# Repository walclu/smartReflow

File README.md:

# smartReflow
## Repository for STM32WB55 based reflow toaster oven controller

The smartReflowV2 is a STm32WB55 based toaster oven reflow controller for reflowing PCBs at home. 

## Features
- 2 SSR outputs
- 2 cooling fan outputs
- 2 MAX31855 temperature ADCs
- Buzzer
- Touch screen (Nextion 2.4" UART Display)
- Bluetooth low energy, onboard chip antenna with matching
- 2 virtual com ports 
- MATLAB data streaming
- EEPROM for storing custom profiles
- PLA drying mode

## Assembly
The PCB was made by JLCPCB and assembled by hand.

## Results
The oven follows the desired temperature profile with only 5% of total error (Reflow state is a little bit delayed at the end).

QFN28 soldering results with 138 C paste profile. No need of rework had to be done.

Finished oven

## ToDos
- Bluetooth works, but an interface (i.e. app) is needed
- Firmware is hard to read
- PCB outline is too small (Nextion Display does not fit nicely onto it)
- EEPROM usage not implemented
- PID autotune code

## License
MIT

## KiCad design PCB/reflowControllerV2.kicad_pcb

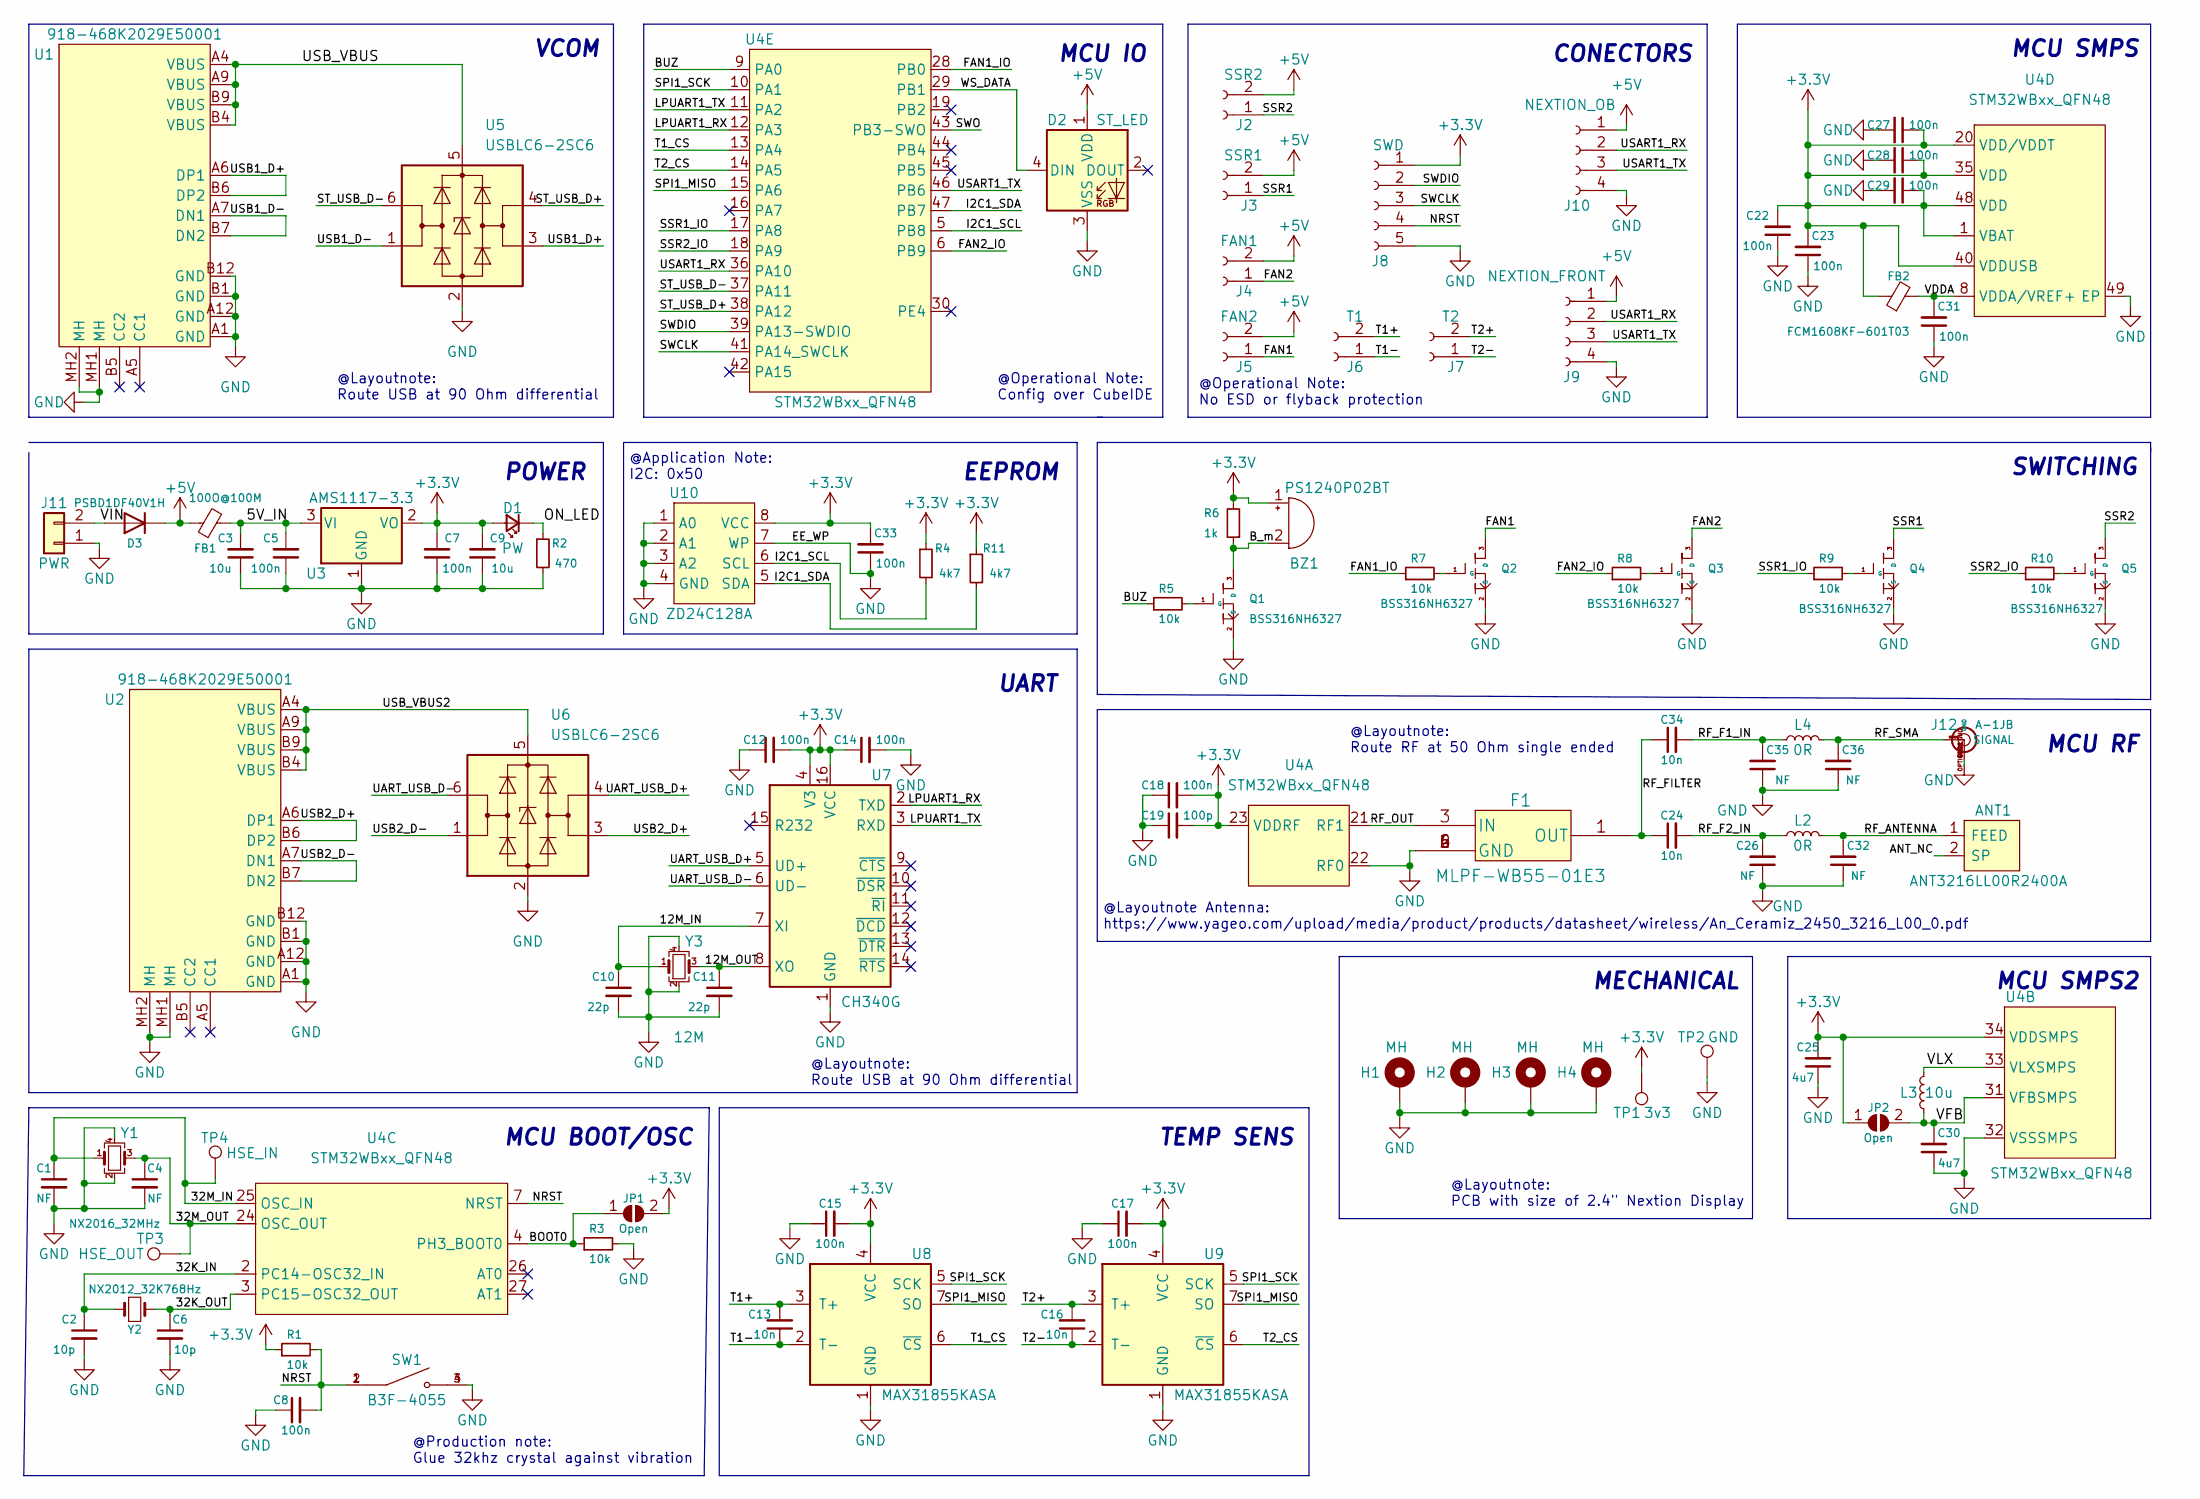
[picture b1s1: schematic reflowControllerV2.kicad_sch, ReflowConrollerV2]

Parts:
ANT1: ANT3216LL00R2400A; Mouser Part Number 603-ANT3216LL00R2400
BZ1: PS1240P02BT; Buzzer_TDK_PS1240P02BT_D12.2mm_H6.5mm
C1, C4, C26, C32, C35, C36: NF; C_0402_1005Metric
C2, C6: 10p; C_0402_1005Metric
C3, C9: 10u; C_0603_1608Metric
C5, C7, C8, C12, C14, C15, C17, C33: 100n; C_0603_1608Metric
C10, C11: 22p; C_0402_1005Metric
C13, C16: 10n; C_0805_2012Metric
C18, C22, C23, C27, C28, C29, C31: 100n; C_0402_1005Metric
C19: 100p; C_0402_1005Metric
C24, C34: 10n; C_0402_1005Metric
C25, C30: 4u7; C_0402_1005Metric
D1: PW; LED_0603_1608Metric
D2: ST_LED; LED_WS2812B_PLCC4_5.0x5.0mm_P3.2mm
D3: PSBD1DF40V1H; D_SOD-123F
F1: MLPF-WB55-01E3
FB1: 100O@100M; L_0603_1608Metric
FB2: FCM1608KF-601T03; L_0603_1608Metric
H1, H2, H3, H4: MH; MountingHole_3.2mm_M3_Pad_Via
J2: SSR2; JST_254_2P_V
J3: SSR1; JST_254_2P_V
J4: FAN1; JST_254_2P_V
J5: FAN2; JST_254_2P_V
J6: T1; JST_254_2P_V
J7: T2; JST_254_2P_V
J8: SWD; JST_254_5P_V
J9: NEXTION_FRONT; JST_254_4P_V
J10: NEXTION_OB; JST_254_4P_H
J11: PWR; TerminalBlock_Phoenix_MKDS-1,5-2_1x02_P5.00mm_Horizontal
J12: A-1JB; AMPHENOL_A-1JB
JP1, JP2: Open; R_0603_1608Metric
L2, L4: 0R; L_0402_1005Metric
L3: 10u; L_0603_1608Metric
Q1, Q2, Q3, Q4, Q5: BSS316NH6327; SOT-23
R1, R5, R7, R8, R9, R10: 10k; R_0603_1608Metric
R2: 470; R_0603_1608Metric
R3: 10k; R_0402_1005Metric
R4, R11: 4k7; R_0603_1608Metric
R6: 1k; R_0603_1608Metric
SW1: B3F-4055; SW_B3F-4055; PARTREV A070-E1-08
TP1: 3v3; TestPoint_Pad_D2.0mm
TP2: GND; TestPoint_Pad_D2.0mm
TP3: HSE_OUT; TestPoint_Pad_D1.0mm
TP4: HSE_IN; TestPoint_Pad_D1.0mm
U1, U2: 918-468K2029E50001
U3: AMS1117-3.3; SOT-223-3_TabPin2
U4: STM32WBxx_QFN48; QFN50P700X700X60-49N
U5, U6: USBLC6-2SC6; SOT-23-6
U7: CH340G; SOIC-16_3.9x9.9mm_P1.27mm
U8, U9: MAX31855KASA; SOIC-8_3.9x4.9mm_P1.27mm
U10: ZD24C128A; SOP-8_3.9x4.9mm_P1.27mm
Y1: NX2016_32MHz; Crystal_SMD_2016-4Pin_2.0x1.6mm
Y2: NX2012_32K768Hz; Crystal_SMD_2012-2Pin_2.0x1.2mm_HandSoldering
Y3: 12M; Crystal_SMD_3225-4Pin_3.2x2.5mm

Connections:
+3V3: BZ1.1 (-), C7.2, C9.2, C12.2, C14.1, C15.2, C17.2, C18.2, C19.2, C22.2, C23.2, C25.2, C27.1, C28.1, C29.1, C33.2, D1.2 (A), FB2.1, J8.1, JP1.2 (B), JP2.1 (A), R1.1, R4.1, R6.2, R11.1, TP1.1, U3.2 (VO), U4.1 (VBAT), U4.20 (VDD/VDDT), U4.23 (VDDRF), U4.34 (VDDSMPS), U4.35 (VDD), U4.40 (VDDUSB), U4.48 (VDD), U7.4 (V3), U7.16 (VCC), U8.4 (VCC), U9.4 (VCC), U10.8 (VCC)
+5V: D2.1 (VDD), D3.1 (K), FB1.1, J2.2, J3.2, J4.2, J5.2, J9.1, J10.1
/5V_IN: C3.2, C5.2, FB1.2, U3.3 (VI)
/12M_IN: C10.1, U7.7 (XI), Y3.1
/12M_OUT: C11.1, U7.8 (XO), Y3.3
/32K_IN: C2.1, U4.2 (PC14-OSC32_IN), Y2.1
/32K_OUT: C6.1, U4.3 (PC15-OSC32_OUT), Y2.2
/32M_IN: C1.1, TP4.1, U4.25 (OSC_IN), Y1.1
/32M_OUT: C4.1, TP3.1, U4.24 (OSC_OUT), Y1.3
/ANT_NC: ANT1.2 (SP)
/BOOT0: JP1.1 (A), R3.1, U4.4 (PH3_BOOT0)
/BUZ: R5.1, U4.9 (PA0)
/B_m: BZ1.2 (+), Q1.3 (D), R6.1
/FAN1: J5.1, Q2.3 (D)
/FAN1_IO: R7.1, U4.28 (PB0)
/FAN2: J4.1, Q3.3 (D)
/FAN2_IO: R8.1, U4.6 (PB9)
/I2C1_SCL: R4.2, U4.5 (PB8), U10.6 (SCL)
/I2C1_SDA: R11.2, U4.47 (PB7), U10.5 (SDA)
/LPUART1_RX: U4.12 (PA3), U7.2 (TXD)
/LPUART1_TX: U4.11 (PA2), U7.3 (RXD)
/NRST: C8.2, J8.4, R1.2, SW1.1, SW1.2, U4.7 (NRST)
/ON_LED: D1.1 (K), R2.1
/RF_ANTENNA: ANT1.1 (FEED), C32.2, L2.2
/RF_F1_IN: C34.2, C35.2, L4.1
/RF_F2_IN: C24.2, C26.2, L2.1
/RF_FILTER: C24.1, C34.1, F1.1 (OUT)
/RF_OUT: F1.3 (IN), U4.21 (RF1)
/RF_SMA: C36.2, J12.SIGNAL, L4.2
/SPI1_MISO: U4.15 (PA6), U8.7 (SO), U9.7 (SO)
/SPI1_SCK: U4.10 (PA1), U8.5 (SCK), U9.5 (SCK)
/SSR1: J3.1, Q4.3 (D)
/SSR1_IO: R9.1, U4.17 (PA8)
/SSR2: J2.1, Q5.3 (D)
/SSR2_IO: R10.1, U4.18 (PA9)
/ST_USB_D+: U4.38 (PA12), U5.4 (I/O2)
/ST_USB_D-: U4.37 (PA11), U5.6 (I/O1)
/SWCLK: J8.3, U4.41 (PA14_SWCLK)
/SWDIO: J8.2, U4.39 (PA13-SWDIO)
/SWO: U4.43 (PB3-SWO)
/T1+: C13.2, J6.2, U8.3 (T+)
/T1-: C13.1, J6.1, U8.2 (T-)
/T1_CS: U4.13 (PA4), U8.6 (~CS)
/T2+: C16.2, J7.2, U9.3 (T+)
/T2-: C16.1, J7.1, U9.2 (T-)
/T2_CS: U4.14 (PA5), U9.6 (~CS)
/UART_USB_D+: U6.4 (I/O2), U7.5 (UD+)
/UART_USB_D-: U6.6 (I/O1), U7.6 (UD-)
/USART1_RX: J9.2, J10.2, U4.36 (PA10)
/USART1_TX: J9.3, J10.3, U4.46 (PB6)
/USB1_D+: U1.A6 (DP1), U1.B6 (DP2), U5.3 (I/O2)
/USB1_D-: U1.A7 (DN1), U1.B7 (DN2), U5.1 (I/O1)
/USB2_D+: U2.A6 (DP1), U2.B6 (DP2), U6.3 (I/O2)
/USB2_D-: U2.A7 (DN1), U2.B7 (DN2), U6.1 (I/O1)
/USB_VBUS: U1.A4 (VBUS), U1.A9 (VBUS), U1.B4 (VBUS), U1.B9 (VBUS), U5.5 (VBUS)
/USB_VBUS2: U2.A4 (VBUS), U2.A9 (VBUS), U2.B4 (VBUS), U2.B9 (VBUS), U6.5 (VBUS)
/VDDA: C31.2, FB2.2, U4.8 (VDDA/VREF+)
/VFB: C30.2, JP2.2 (B), L3.1, U4.31 (VFBSMPS)
/VIN: D3.2 (A), J11.2
/VLX: L3.2, U4.33 (VLXSMPS)
/WS_DATA: D2.4 (DIN), U4.29 (PB1)
GND: C1.2, C2.2, C3.1, C4.2, C5.1, C6.2, C7.1, C8.1, C9.1, C10.2, C11.2, C12.1, C14.2, C15.1, C17.1, C18.1, C19.1, C22.1, C23.1, C25.1, C26.1, C27.2, C28.2, C29.2, C30.1, C31.1, C32.1, C33.1, C35.1, C36.1, D2.3 (VSS), F1.2 (GND), F1.4 (GND), F1.5 (GND), F1.6 (GND), H1.1, H2.1, H3.1, H4.1, J8.5, J9.4, J10.4, J11.1, J12.GND1 (GND), J12.GND2 (GND), J12.OPTIONAL_GND (GND), Q1.2 (S), Q2.2 (S), Q3.2 (S), Q4.2 (S), Q5.2 (S), R2.2, R3.2, SW1.3, SW1.4, TP2.1, U1.A1 (GND), U1.A12 (GND), U1.B1 (GND), U1.B12 (GND), U1.MH1 (MH), U1.MH2 (MH), U2.A1 (GND), U2.A12 (GND), U2.B1 (GND), U2.B12 (GND), U2.MH1 (MH), U2.MH2 (MH), U3.1 (GND), U4.22 (RF0), U4.32 (VSSSMPS), U4.49 (EP), U5.2 (GND), U6.2 (GND), U7.1 (GND), U8.1 (GND), U9.1 (GND), U10.1 (A0), U10.2 (A1), U10.3 (A2), U10.4 (GND), U10.7 (WP), Y1.2, Y1.4, Y3.2, Y3.4
unnamed: Q1.1 (G), R5.2
unnamed: Q2.1 (G), R7.2
unnamed: Q3.1 (G), R8.2
unnamed: Q4.1 (G), R9.2
unnamed: Q5.1 (G), R10.2

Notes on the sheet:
EEPROM
MCU SMPS2
@Operational Note: No ESD or flyback protection
MECHANICAL
@Layoutnote: Route RF at 50 Ohm single ended
@Layoutnote: Route USB at 90 Ohm differential
TEMP SENS
@Layoutnote Antenna: https://www.yageo.com/upload/media/product/products/datasheet/wireless/An_Ceramiz_2450_3216_L00_0.pdf
SWITCHING
MCU BOOT/OSC
MCU IO
UART
CONECTORS
MCU SMPS
VCOM
@Production note: Glue 32khz crystal against vibration
@Operational Note: Config over CubeIDE
MCU RF
@Layoutnote: PCB with size of 2.4" Nextion Display
POWER
@Application Note: I2C: 0x50

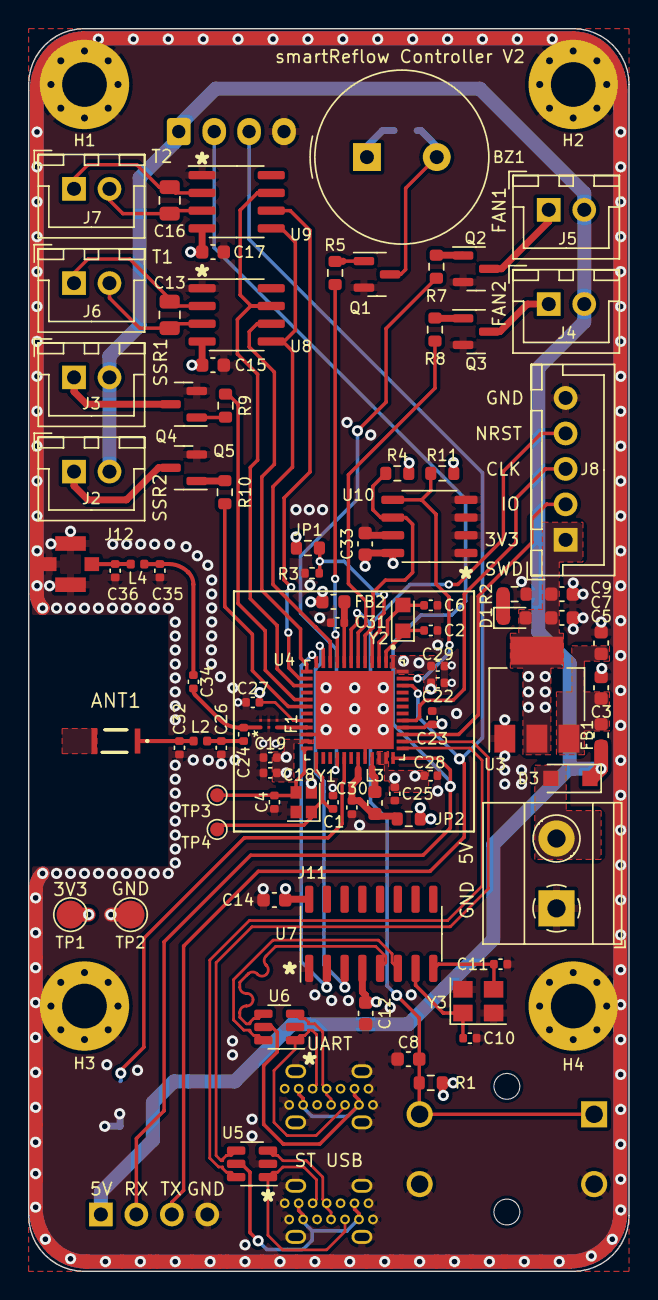
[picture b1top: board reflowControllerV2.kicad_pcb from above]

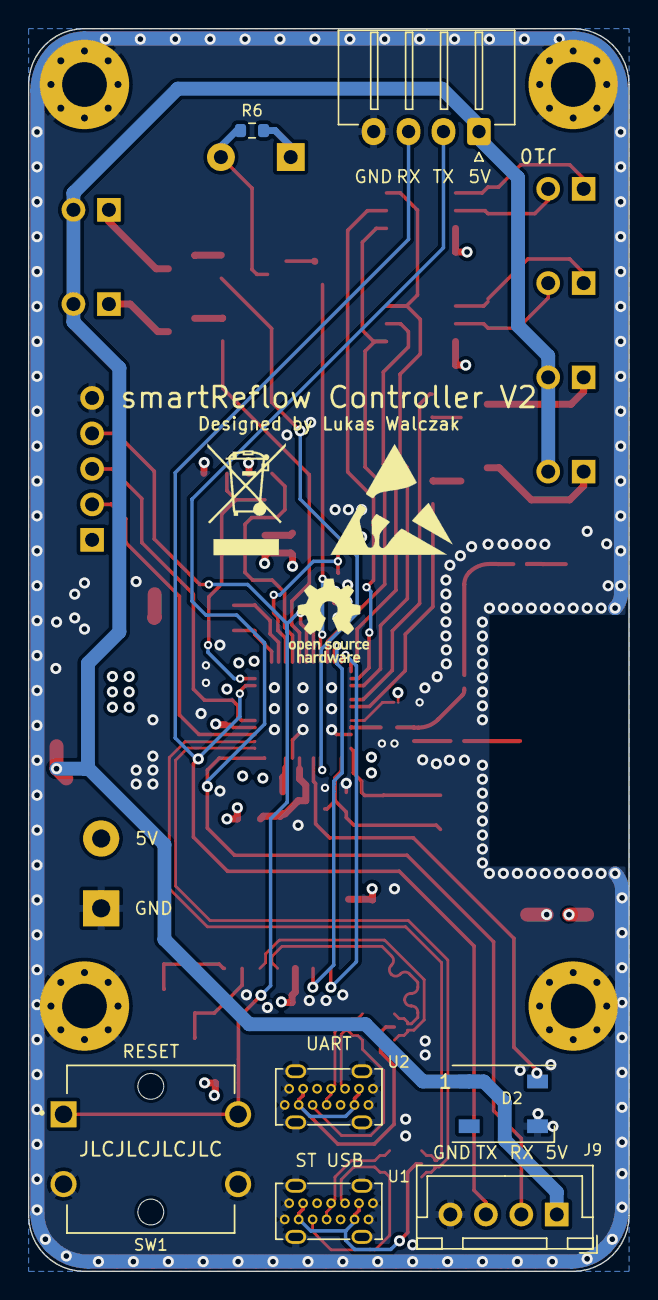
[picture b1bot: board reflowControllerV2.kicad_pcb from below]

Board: 4 copper layers, 43.0 x 89.0 mm, 96 parts (7 on the bottom side), 65 nets.

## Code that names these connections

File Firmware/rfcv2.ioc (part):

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Mcu.Name=STM32WB55CEUx
Mcu.Package=UFQFPN48
Mcu.UserName=STM32WB55CEUx
PA0.GPIOParameters=GPIO_Label
PA0.GPIO_Label=BUZ
PA0.Signal=S_TIM2_CH1
PA1.Mode=RX_Only_Simplex_Unidirect_Master
PA1.Signal=SPI1_SCK
PA10.Mode=Asynchronous
PA10.Signal=USART1_RX
PA11.Mode=Device
PA11.Signal=USB_DM
PA12.Mode=Device
PA12.Signal=USB_DP
PA13.Mode=Serial_Wire
PA13.Signal=SYS_JTMS-SWDIO
PA14.Mode=Serial_Wire
PA14.Signal=SYS_JTCK-SWCLK
PA2.Mode=Asynchronous
PA2.Signal=LPUART1_TX
PA3.Mode=Asynchronous
PA3.Signal=LPUART1_RX
PA4.GPIOParameters=GPIO_Label
PA4.GPIO_Label=T1_CS
PA4.Signal=GPIO_Output
PA5.GPIOParameters=GPIO_Label
PA5.GPIO_Label=T2_CS
PA5.Signal=GPIO_Output
PA6.Mode=RX_Only_Simplex_Unidirect_Master
PA6.Signal=SPI1_MISO
PA8.GPIOParameters=GPIO_Label
PA8.GPIO_Label=SSR1_IO
PA8.Signal=S_TIM1_CH1
PA9.GPIOParameters=GPIO_Label
PA9.GPIO_Label=SSR2_IO
PA9.Signal=S_TIM1_CH2
PB0.GPIOParameters=GPIO_Label
PB0.GPIO_Label=FAN1_IO
PB0.Signal=GPIO_Output
PB1.GPIOParameters=GPIO_Label
PB1.GPIO_Label=WS_DATA
PB1.Signal=GPIO_Output
PB6.Mode=Asynchronous
PB6.Signal=USART1_TX
PB7.Mode=I2C
PB7.Signal=I2C1_SDA
PB8.Mode=I2C
PB8.Signal=I2C1_SCL
PB9.GPIOParameters=GPIO_Label
PB9.GPIO_Label=FAN2_IO
PB9.Signal=GPIO_Output
PC14-OSC32_IN.Mode=LSE-External-Oscillator
PC14-OSC32_IN.Signal=RCC_OSC32_IN
PC15-OSC32_OUT.Mode=LSE-External-Oscillator
PC15-OSC32_OUT.Signal=RCC_OSC32_OUT
RCC.HSE_VALUE=32000000
RCC.SYSCLKFreq_VALUE=64000000
RCC.SYSCLKSource=RCC_SYSCLKSOURCE_PLLCLK
board=custom

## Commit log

2022-04-21 Added current src files
2022-04-21 Changed PCB dir name
2022-04-21 Removed old simulations from other project
2022-04-21 Renamed Firmware dir, still developing on EVALBoard
2022-04-22 PCB antenna removed
2022-04-23 Further component placing
2022-04-26 RF Routing, Guard Ring, component placing, switching to mosfets
2022-04-27 Started layout, critical sections first
2022-04-27 Layout done, improovements needed
2022-04-29 PCB finalized, Gerbers created, Firmware dir renamed
2022-04-29 Recreated Gerbers with removed order number
2022-05-04 Firmware stably working
2022-05-04 MATLAB streamer class and files working
2022-05-04 Added loading, main, setting and reflow page, modfied uart callbacks
2022-05-04 PCB backup
2022-05-04 Removed old MATLAB code, not longer needed
2022-05-26 Added 3d models for printing front and accessories
2022-05-26 Added example bin for nucleo dongle (BLE Test)
2022-05-26 Added current Firmware version in CubeIDE
2022-05-26 Backups, step model of PCB
2022-05-26 Added p nucleo wb55 ds
2022-05-26 Removed old Firmware project
2022-06-13 PLA heating and 160 deg paste working reliably
2022-06-13 PLA heating page added
2022-06-13 Backups
2022-06-13 Few changes
2022-06-13 Added pictures of PCB, mechanicals and results
2022-06-23 Assembly information
2022-06-23 Readme
2022-08-06 Reorganized schematic
2023-01-26 No change
2023-01-26 Added patched reflow_oven firmware project
